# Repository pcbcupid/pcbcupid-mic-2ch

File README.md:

# pcbcupid-mic-2ch
TDK ICS 43434 based 2CH I2S digital MIC, which can be used as a replacement for the obsolete INMP441 

This repo contains open source PCB files for PCBCUPID GSense Touch Slider Module <br/>
This particular PCB is designed using Kicad v9.0

**This design has been built and tested successfully!**
For more details, check out the product pages at

   * [Gsesnse-2ch-mic](https://shop.pcbcupid.com/product/gs002/)
   * [Docs](https://learn.pcbcupid.com/boards/g-sense/ics43434-2ch)
     
We are here to build India's largest open source hardware community, If you like to support
please consider buying the product from the above link!

[Creative Commons Attribution, Share-Alike license](https://creativecommons.org/licenses/by-sa/4.0/deed.en)
All text above must be included in any redistribution

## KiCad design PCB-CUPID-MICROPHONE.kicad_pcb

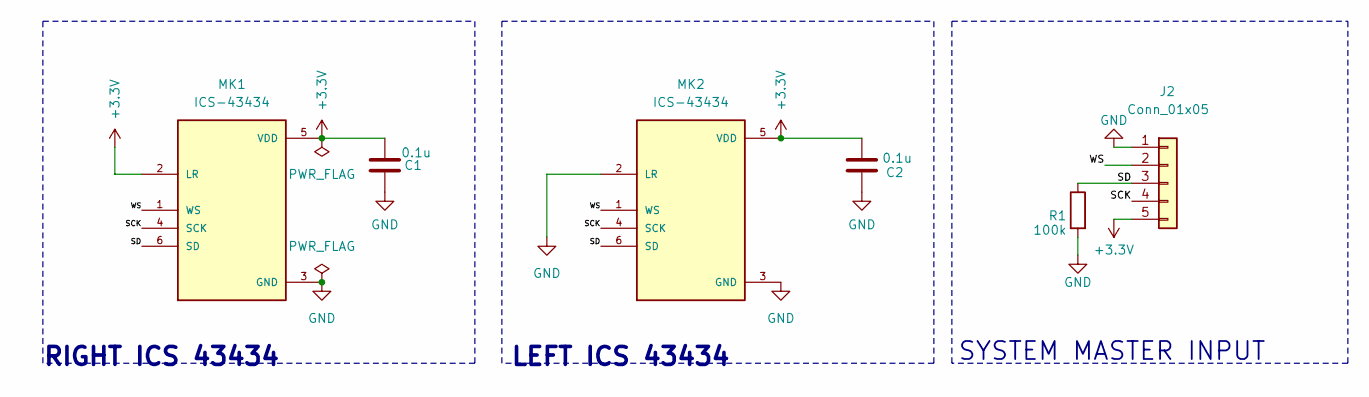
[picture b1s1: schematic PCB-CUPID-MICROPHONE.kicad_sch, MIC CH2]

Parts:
C1, C2: 0.1u; C_0603_1608Metric
J2: Conn_01x05; PinHeader_1x05_P2.54mm_Vertical
MK1, MK2: ICS-43434; MIC_ICS-43434
R1: 100k; R_0603_1608Metric

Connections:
+3.3V: C1.2, C2.1, J2.5, MK1.2 (LR), MK1.5 (VDD), MK2.5 (VDD)
/SCK: J2.4, MK1.4 (SCK), MK2.4 (SCK)
/SD: J2.3, MK1.6 (SD), MK2.6 (SD), R1.1
/WS: J2.2, MK1.1 (WS), MK2.1 (WS)
GND: C1.1, C2.2, J2.1, MK1.3 (GND), MK2.2 (LR), MK2.3 (GND), R1.2

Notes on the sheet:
SYSTEM MASTER INPUT
LEFT ICS 43434
RIGHT ICS 43434

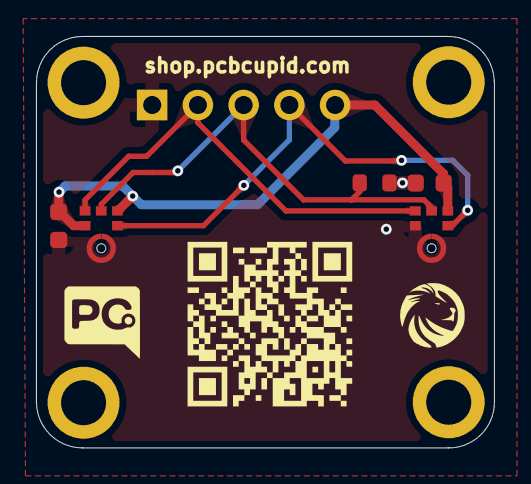
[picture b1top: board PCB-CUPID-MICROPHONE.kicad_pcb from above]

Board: 2 copper layers, 25.4 x 22.9 mm, 6 parts (0 on the bottom side), 5 nets.

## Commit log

2026-06-30 updated pcbcupid-mic-2ch files
